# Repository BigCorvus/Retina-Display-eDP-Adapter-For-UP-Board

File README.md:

# Retina-Display-eDP-Adapter-For-UP-Board
This project contains the design files for an eDP adapter and backlight driver for iPad 3 retina displays. These have  2,048 by 1,536 (2K) resolution and are 9.7 inch in diagonal. They can be ripped out of bricked or defective ipads or bought as new replacement parts for about 40$. With an adapter such as this one http://abusemark.com/store/index.php?main_page=product_info&products_id=53&zenid=li1so9u2k8e7n3u8q3j7j0uqg2 you should be able to use 7.9 inch iPad mini screens too. Capacitive touch overlays for the 9.7 inch screens with i2c to USB converters can be found on aliexpress.

The adapter and backlight driver board is based on the Adafruit Qualia driver (https://learn.adafruit.com/qualia-high-res-displayport-desktop-monitor?view=all#overview). The PCB has been made smaller and the 3.3V buck regulator, ATtiny backlight control as well as the bulky display port connector have been removed since most single board computers already provide 3.3V as well as backlight control. The board can be used for any single board computer with eDP interface by soldering bare wires to the appropriate connector. I'm using this with an UP core with Windows 10. After some automatic driver installations in the background, the PWM dimming function started to work perfectly well. The retina display connectors can be found on ebay and are quite cheap. And yes, they can be hand soldered. Just use enough good quality flux.

A .brd file for a connector for CN31 of the UP board or UP core is included, which can be manufactured by the new OSH Park flex service and costs next to nothing. The 5 differential pairs as well as wires for the 3.3V supply and control lines are soldered directly to the flex PCB using 30AWG solid core wires. Note that the flex PCB seems to be a little too thick for the connector to close properly, but the friction fit seems to be sufficient.

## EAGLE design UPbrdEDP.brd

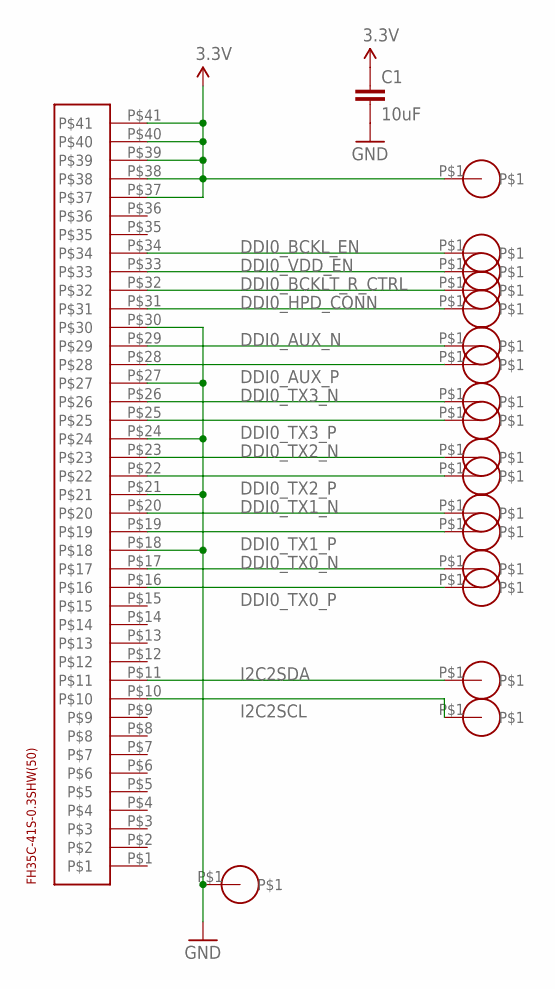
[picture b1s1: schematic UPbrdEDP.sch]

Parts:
C1: 10uF; 0603-CAP
U$1: FH35C-41S-0.3SHW(50)
U$2, U$3, U$4, U$5, U$6, U$7, U$8, U$9, U$10, U$11, U$12, U$13, U$14, U$15, U$16, U$17, U$18, U$19: SOLDERPAD

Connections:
3.3V: C1.1, U$1.P$37, U$1.P$38, U$1.P$39, U$1.P$40, U$1.P$41, U$18.P$1
DDI0_AUX_N: U$1.P$29, U$13.P$1
DDI0_AUX_P: U$1.P$28, U$12.P$1
DDI0_BCKLT_R_CTRL: U$1.P$32, U$15.P$1
DDI0_BCKL_EN: U$1.P$34, U$17.P$1
DDI0_HPD_CONN: U$1.P$31, U$14.P$1
DDI0_TX0_N: U$1.P$17, U$5.P$1
DDI0_TX0_P: U$1.P$16, U$4.P$1
DDI0_TX1_N: U$1.P$20, U$7.P$1
DDI0_TX1_P: U$1.P$19, U$6.P$1
DDI0_TX2_N: U$1.P$23, U$9.P$1
DDI0_TX2_P: U$1.P$22, U$8.P$1
DDI0_TX3_N: U$1.P$26, U$11.P$1
DDI0_TX3_P: U$1.P$25, U$10.P$1
DDI0_VDD_EN: U$1.P$33, U$16.P$1
GND: C1.2, U$1.P$18, U$1.P$21, U$1.P$24, U$1.P$27, U$1.P$30, U$19.P$1
I2C2SCL: U$1.P$10, U$3.P$1
I2C2SDA: U$1.P$11, U$2.P$1

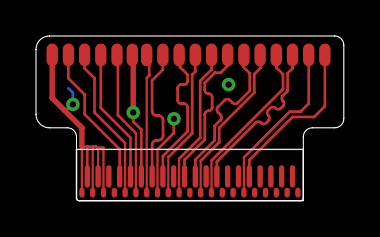
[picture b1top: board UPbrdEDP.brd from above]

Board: 2 copper layers, 17.1 x 9.2 mm, 20 parts (1 on the bottom side), 18 nets.

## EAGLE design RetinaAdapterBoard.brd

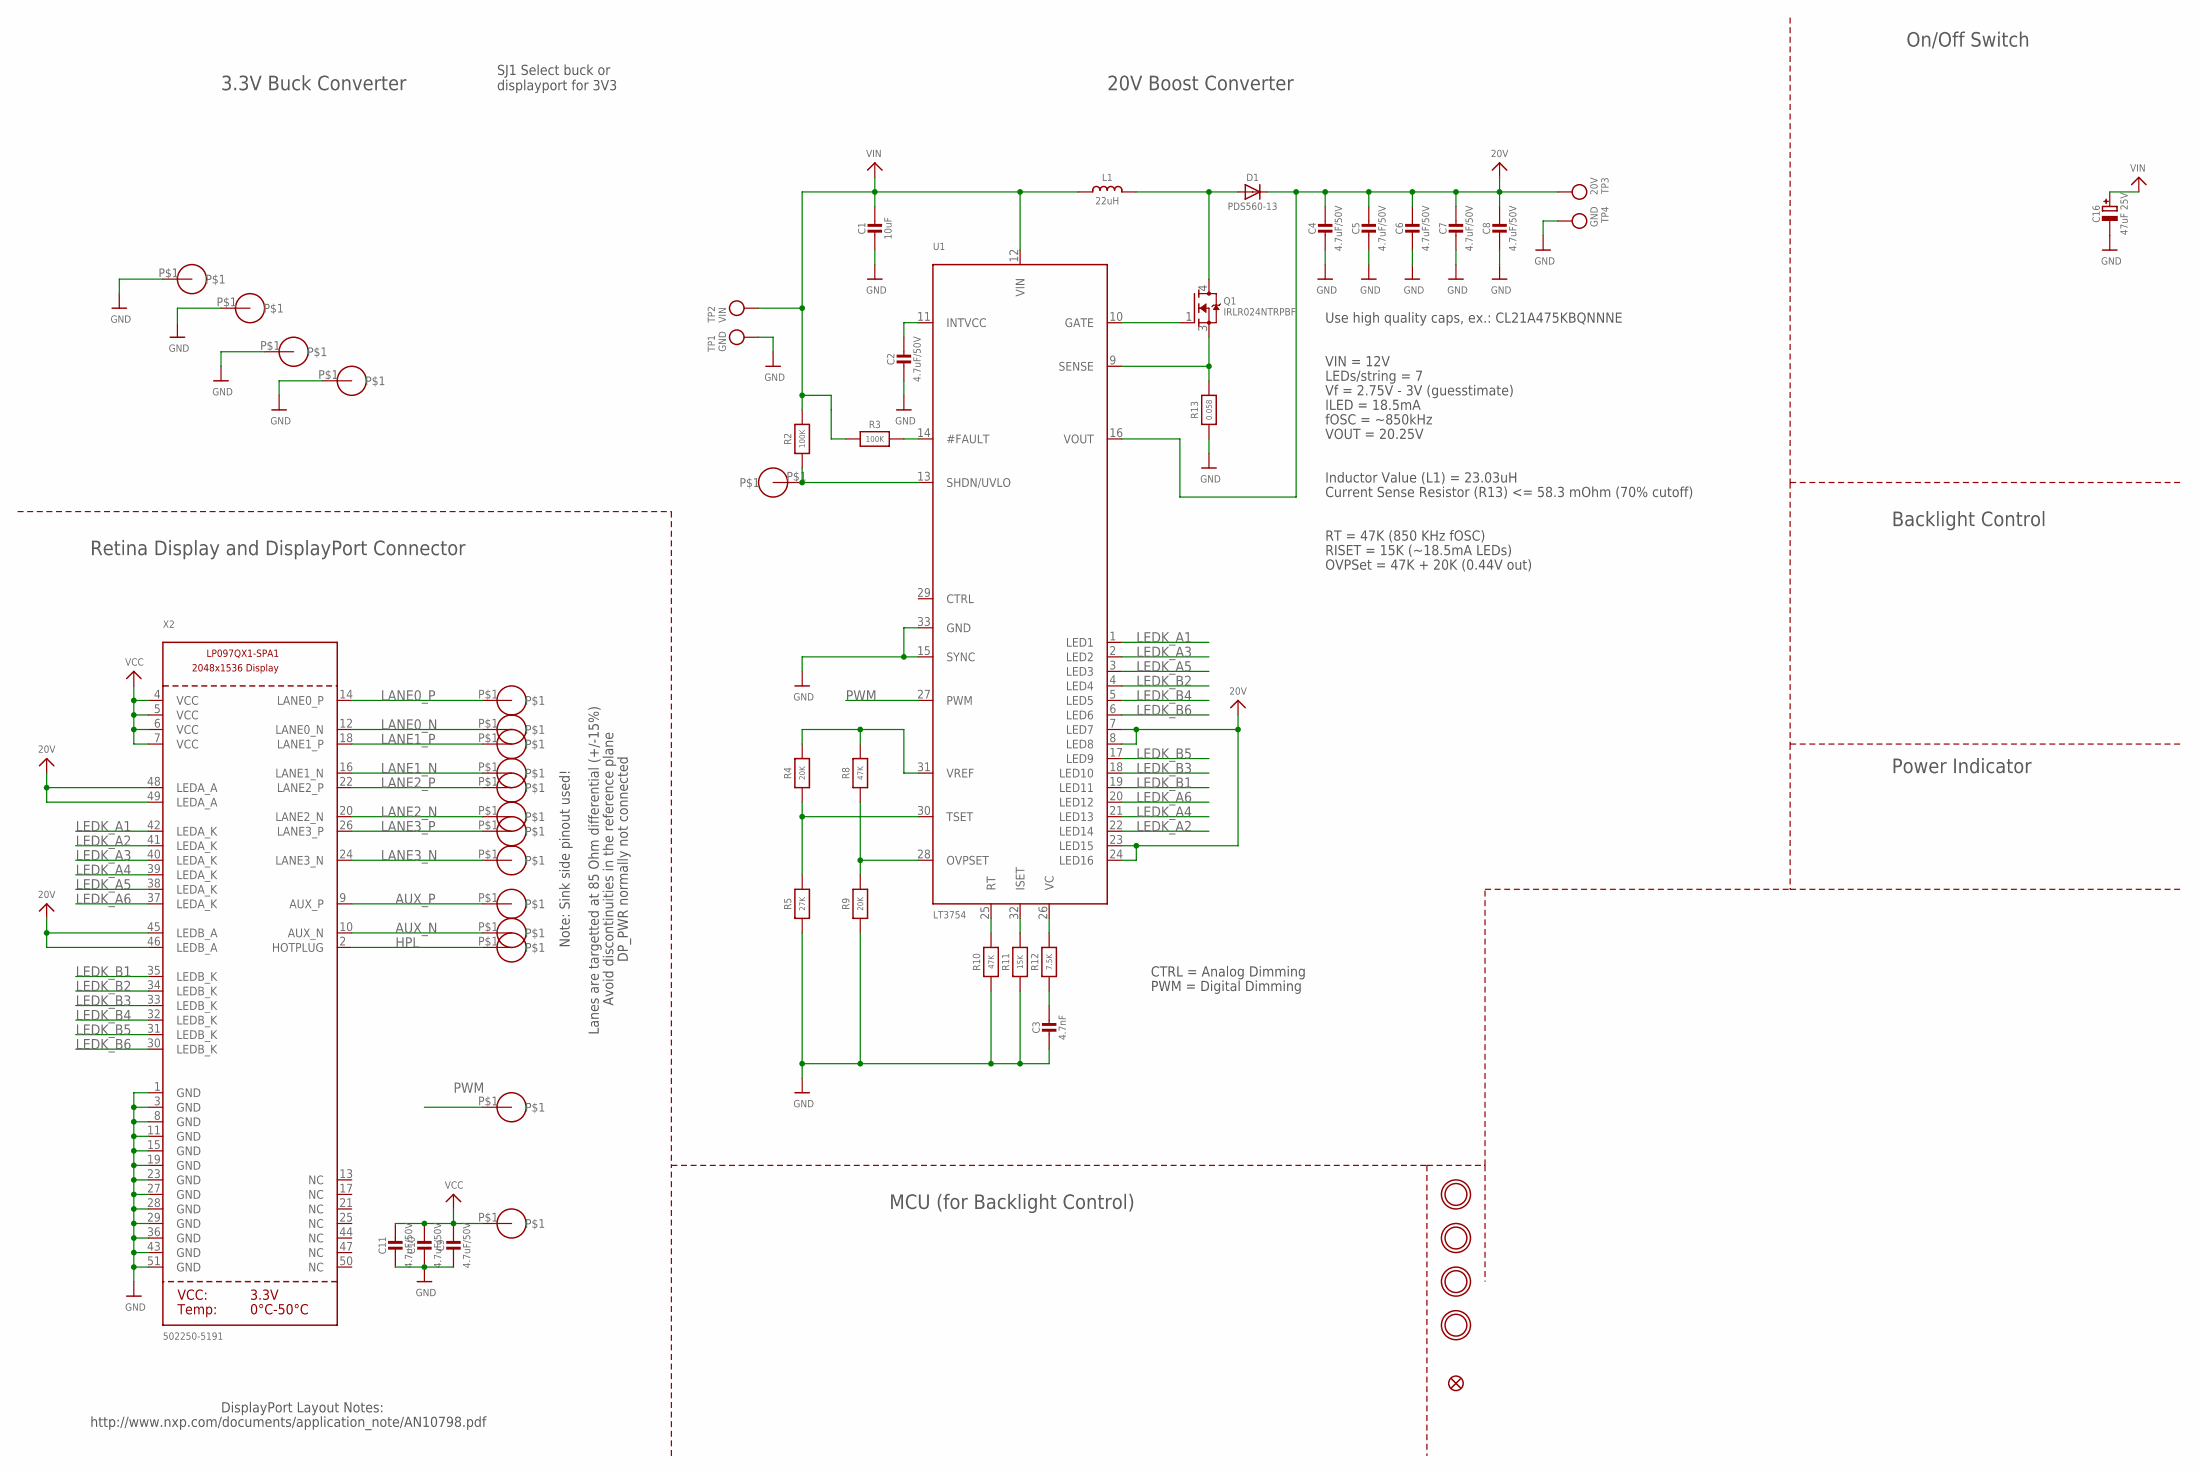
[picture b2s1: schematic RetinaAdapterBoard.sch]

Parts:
C1: 10uF; _0805
C2, C4, C5, C6, C7, C8, C9, C10, C11: 4.7uF/50V; _0805
C3: 4.7nF; _0805
C16: 47uF 25V; PANASONIC_C
D1: PDS560-13; POWERDI-5
FID3: FIDUCIAL""; FIDUCIAL_1MM
L1: 22uH; INDUCTOR_6X6MM_SUMIDA_CDRH5D28
Q1: IRLR024NTRPBF; DPAK
R2, R3: 100K; _0805
R4, R9: 20K; _0805
R5: 27K; _0805
R8, R10: 47K; _0805
R11: 15K; _0805
R12: 7.5K; _0805
R13: 0.058; 2512
TP1, TP4: GND; TESTPOINT_ROUND_1MM
TP2: VIN; TESTPOINT_ROUND_1MM
TP3: 20V; TESTPOINT_ROUND_1MM
U1: LT3754; QFN32_5MM
U$1, U$4, U$9, U$10, U$13, U$15, U$43, U$46, U$47, U$48, U$49, U$50, U$51, U$52, U$53, U$54, U$55, U$57: SOLDERPAD
U$11, U$32, U$33, U$34: MOUNTINGHOLE3.0THIN; MOUNTINGHOLE_3.0_PLATEDTHIN
X2: 502250-5191; FPC_51PIN_502250-5191_EXT

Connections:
20V: C4.1, C5.1, C6.1, C7.1, C8.1, D1.C, TP3.P$1, U1.7 (LED7), U1.8 (LED8), U1.16 (VOUT), U1.23 (LED15), U1.24 (LED16), X2.45 (LEDB_A), X2.46 (LEDB_A), X2.48 (LEDA_A), X2.49 (LEDA_A)
AUX_N: U$1.P$1, X2.10 (AUX_N)
AUX_P: U$43.P$1, X2.9 (AUX_P)
GND: C1.2, C2.2, C3.2, C4.2, C5.2, C6.2, C7.2, C8.2, C9.2, C10.2, C11.2, C16.-, R5.1, R9.1, R10.1, R11.1, R13.1, TP1.P$1, TP4.P$1, U1.15 (SYNC), U1.33 (GND), U$10.P$1, U$13.P$1, U$15.P$1, U$55.P$1, X2.1 (GND), X2.3 (GND), X2.8 (GND), X2.11 (GND), X2.15 (GND), X2.19 (GND), X2.23 (GND), X2.27 (GND), X2.28 (GND), X2.29 (GND), X2.36 (GND), X2.43 (GND), X2.51 (GND)
HPL: U$54.P$1, X2.2 (HOTPLUG)
LANE0_N: U$52.P$1, X2.12 (LANE0_N)
LANE0_P: U$53.P$1, X2.14 (LANE0_P)
LANE1_N: U$50.P$1, X2.16 (LANE1_N)
LANE1_P: U$51.P$1, X2.18 (LANE1_P)
LANE2_N: U$48.P$1, X2.20 (LANE2_N)
LANE2_P: U$49.P$1, X2.22 (LANE2_P)
LANE3_N: U$46.P$1, X2.24 (LANE3_N)
LANE3_P: U$47.P$1, X2.26 (LANE3_P)
LEDK_A1: U1.1 (LED1), X2.42 (LEDA_K)
LEDK_A2: U1.22 (LED14), X2.41 (LEDA_K)
LEDK_A3: U1.2 (LED2), X2.40 (LEDA_K)
LEDK_A4: U1.21 (LED13), X2.39 (LEDA_K)
LEDK_A5: U1.3 (LED3), X2.38 (LEDA_K)
LEDK_A6: U1.20 (LED12), X2.37 (LEDA_K)
LEDK_B1: U1.19 (LED11), X2.35 (LEDB_K)
LEDK_B2: U1.4 (LED4), X2.34 (LEDB_K)
LEDK_B3: U1.18 (LED10), X2.33 (LEDB_K)
LEDK_B4: U1.5 (LED5), X2.32 (LEDB_K)
LEDK_B5: U1.17 (LED9), X2.31 (LEDB_K)
LEDK_B6: U1.6 (LED6), X2.30 (LEDB_K)
unnamed: C2.1, U1.11 (INTVCC)
unnamed: R2.1, U1.13 (SHDN/UVLO), U$9.P$1
unnamed: R3.2, U1.14 (#FAULT)
unnamed: R12.2, U1.26 (VC)
unnamed: C3.1, R12.1
unnamed: R4.1, R5.2, U1.30 (TSET)
unnamed: R4.2, R8.2, U1.31 (VREF)
unnamed: R8.1, R9.2, U1.28 (OVPSET)
unnamed: R10.2, U1.25 (RT)
unnamed: R11.2, U1.32 (ISET)
unnamed: Q1.3 (S), R13.2, U1.9 (SENSE)
unnamed: Q1.1 (G), U1.10 (GATE)
unnamed: D1.A1 (A), D1.A2 (A), L1.P$2 (2), Q1.4 (D)
PWM: U1.27 (PWM), U$57.P$1
VCC: C9.1, C10.1, C11.1, U$4.P$1, X2.4 (VCC), X2.5 (VCC), X2.6 (VCC), X2.7 (VCC)
VIN: C1.1, C16.+, L1.P$1 (1), R2.2, R3.1, TP2.P$1, U1.12 (VIN)

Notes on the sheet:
Note: Sink side pinout used!
DP_PWR normally not connected
Lanes are targetted at 85 Ohm differential (+/-15%)
Avoid discontinuities in the reference plane
DisplayPort Layout Notes:
http://www.nxp.com/documents/application_note/AN10798.pdf
Use high quality caps, ex.: CL21A475KBQNNNE
Inductor Value (L1) = 23.03uH
VIN = 12V
LEDs/string = 7
Vf = 2.75V - 3V (guesstimate)
ILED = 18.5mA
VOUT = 20.25V
fOSC = ~850kHz
Current Sense Resistor (R13) <= 58.3 mOhm (70% cutoff)
RT = 47K (850 KHz fOSC)
RISET = 15K (~18.5mA LEDs)
OVPSet = 47K + 20K (0.44V out)
20V Boost Converter
MCU (for Backlight Control)
On/Off Switch
Retina Display and DisplayPort Connector
3.3V Buck Converter
CTRL = Analog Dimming
PWM = Digital Dimming
Backlight Control
Power Indicator
SJ1 Select buck or displayport for 3V3

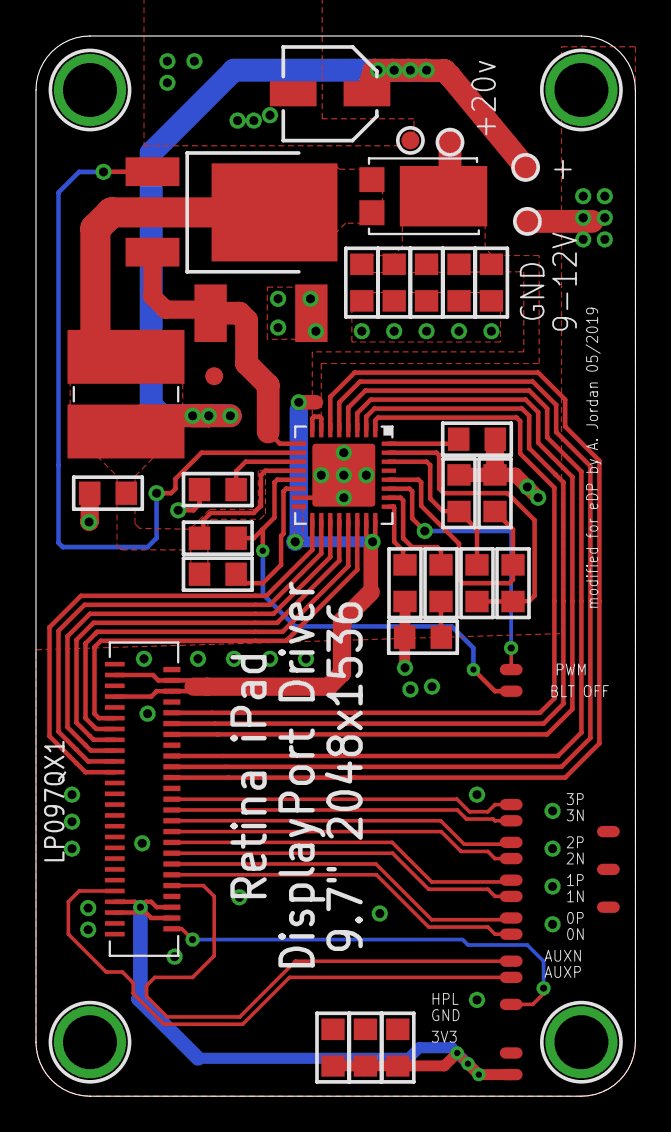
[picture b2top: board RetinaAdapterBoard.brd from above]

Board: 2 copper layers, 33.3 x 58.9 mm, 54 parts (0 on the bottom side), 41 nets.

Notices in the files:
parts and their libraries:
microbuilder: This work is placed in the public domain, and may be freely used for commercial and non-commercial work with the following conditions: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
SparkFun-Capacitors: Licensing: Creative Commons ShareAlike 4.0 International - https://creativecommons.org/licenses/by-sa/4.0
